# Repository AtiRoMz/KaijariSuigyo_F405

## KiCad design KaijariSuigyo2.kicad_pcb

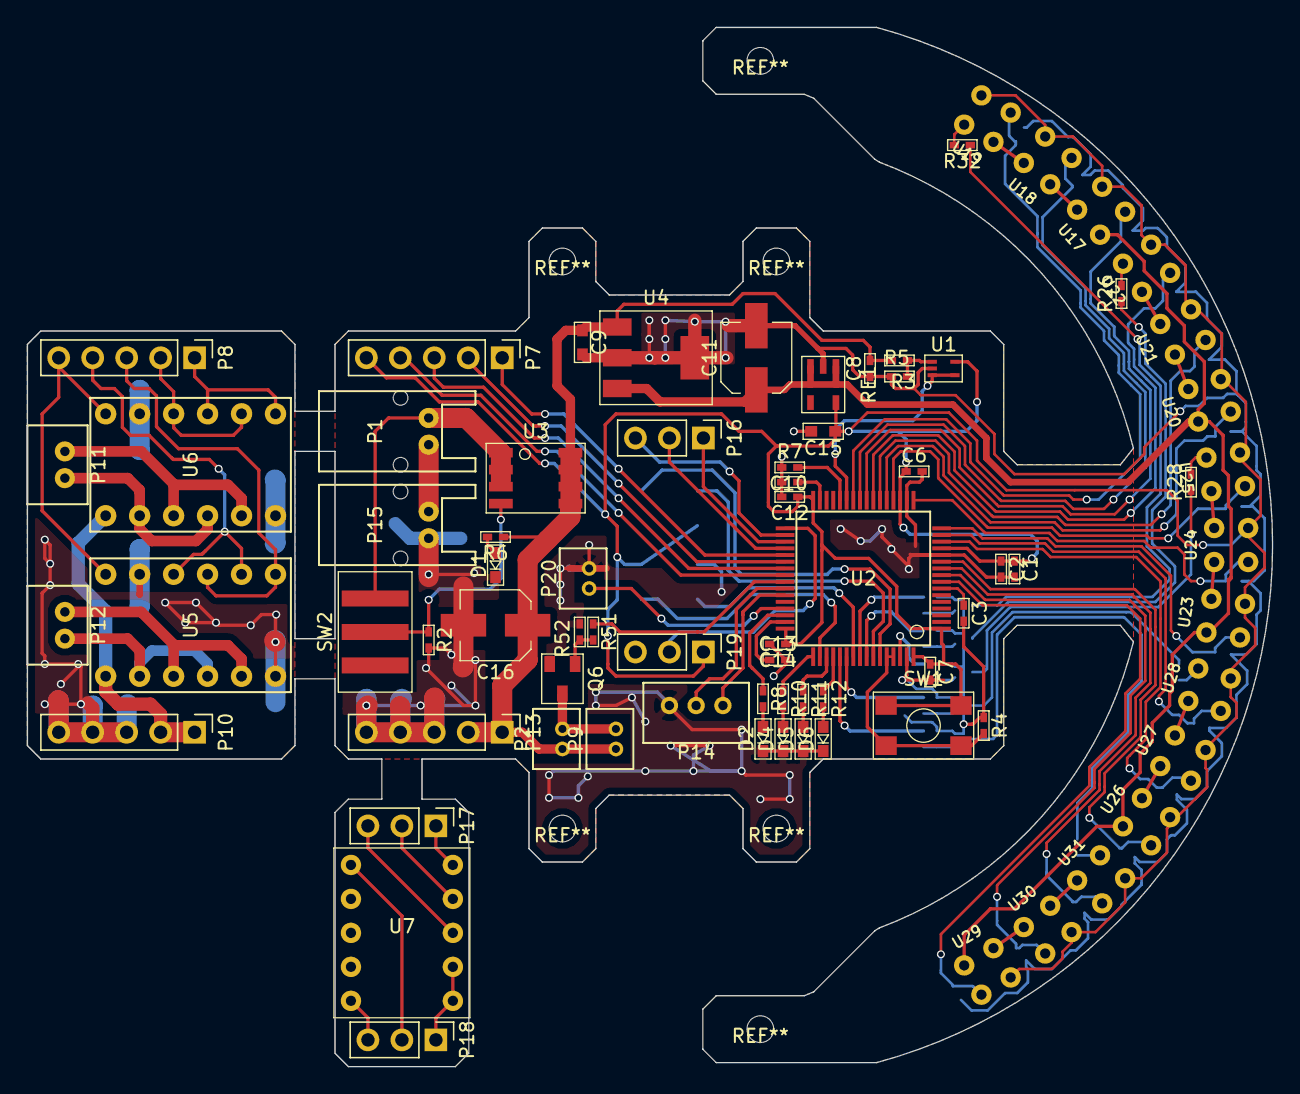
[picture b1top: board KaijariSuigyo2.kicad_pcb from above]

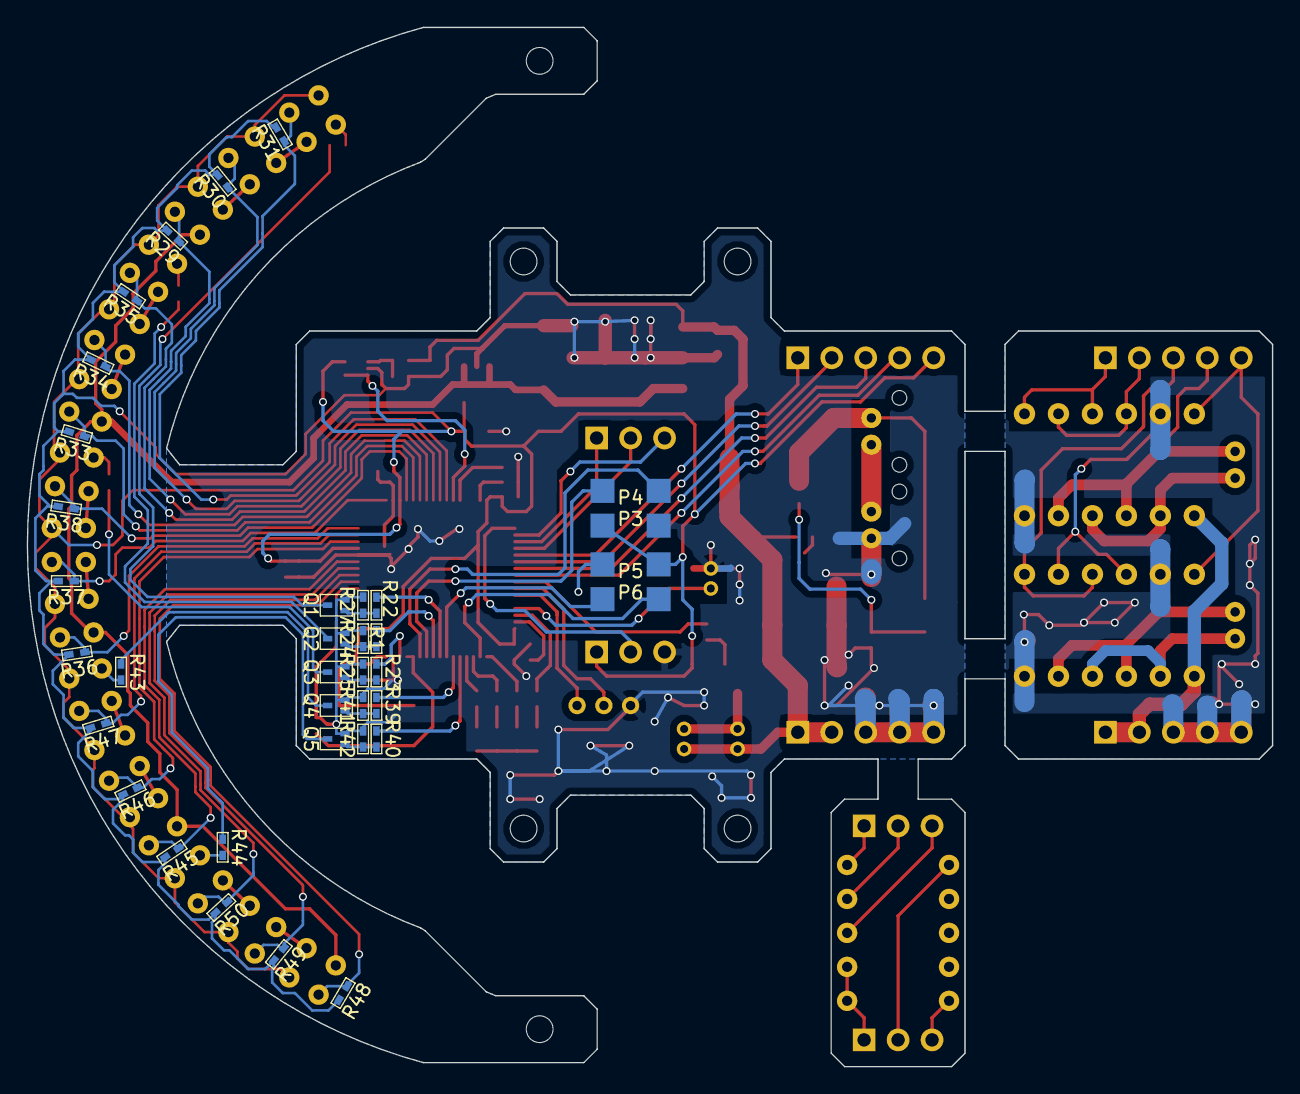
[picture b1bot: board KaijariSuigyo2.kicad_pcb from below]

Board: 2 copper layers, 93.1 x 77.7 mm, 112 parts (36 on the bottom side), 103 nets.

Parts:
C1: 1u; My_1005
C2, C3, C6, C7, C8, C12, C14: 0.1u; My_1005
C9: 0.47u; My_1608
C10, C13: 2.2u; My_1005
C11, C16: 47u; My_AlumiCapa_5mm
C15: 4.7u; My_1608
D1: Led_Small; My_LED_1608
D2, D4, D5, D6: LED; My_LED_1608
P1, P15: CONN_BATT; PA_2
P2: LEFT_FAN; ZH_2
P3, P4, P5, P6: ENC_CON; ENC_CON_ver2
P7, P8, P10, P13: CONN_01X05; Pin_Header_Straight_1x05_Pitch2.54mm
P9: RIGHT_FAN; ZH_2
P11: MOTOR_R; PH_2
P12: MOTOR_L; PH_2
P14: CONN_01X03; PH_3
P16, P17, P18, P19: CONN_01X03; Pin_Header_Straight_1x03_Pitch2.54mm
P20: CONN_01X02; ZH_2
Q1, Q2, Q3, Q4, Q5: IRLML6344; RUM003N02
Q6: IRLML6344; My_SOT-23
R1, R22, R23, R39, R40: 470; My_1005
R2: 47k; My_1005
R3: 4.7k; My_1005
R4, R5, R7, R52: 10k; My_1005
R6, R29, R30, R31, R33, R34, R35, R36, R37, R38, R45, R46, R47, R48, R49, R50: 1k; My_1005
R8, R10, R11, R12, R51: 100; My_1005
R24, R25, R27, R41, R42: 470k; My_1005
R26, R28, R32, R43, R44: 10; My_1005
RE1: MIC5219; My_SOT-23-5
SW1: SW_PUSH; TL3305
SW2: SWITCH_INV; CL-SB-22A-01
U1: BU7255HFV; My_HVSOF5
U2: STM32F405RGT6; LQFP64
U3: STS7PF30L; My_SOIC-8_3.9x4.9_Pitch1.27mm
U4: LM2940IMP; My_SOT-223
U5, U6: DRV8835_Module
U7: MPU9250_Module; MPU9250Module
U17, U18, U19, U20, U21, U22, U23, U24, U25, U26, U27, U28, U29, U30, U31: PHOTOTRANSISTOR; LBR127HLD

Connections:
+3V3: C1.1, C2.1, C6.1, C7.1, C12.1, C14.1, C15.1, P3.2, P5.2, P7.5, P19.1, RE1.5, SW1.1, U1.5, U2.1, U2.13, U2.19, U2.32, U2.48, U2.64, U17.4, U18.4, U19.4, U20.4, U21.4, U22.4, U23.4, U24.4, U25.4, U26.4, U27.4, U28.4, U29.4, U30.4, U31.4
+5V: C11.1, RE1.1, RE1.3, U4.3, U17.1, U20.1, U23.1, U26.1, U29.1
+BATT: C8.2, C9.1, C16.1, P2.1, P9.1, P13.1, P13.2, R5.2, R6.1, U3.5, U3.6, U3.7, U3.8, U4.1
BATT_REF: U1.3, U1.4, U2.27
CS: P19.2, U2.33
ENCA_LEFT: P4.1, U2.58
ENCA_RIGHT: P6.1, U2.50
ENCB_LEFT: P4.2, U2.59
ENCB_RIGHT: P6.2, U2.55
FAN_MOTOR: R51.1, U2.41
GND: C1.2, C2.2, C3.2, C6.2, C7.2, C8.1, C9.2, C10.1, C11.2, C12.2, C13.2, C14.2, C15.2, C16.2, D1.1, D2.1, D4.1, D5.1, D6.1, P3.1, P5.1, P13.3, P13.4, P13.5, P14.3, P15.1, P19.3, P20.2, Q1.2, Q2.2, Q3.2, Q4.2, Q5.2, Q6.2, R2.2, R3.1, R4.1, R7.1, R24.2, R25.2, R27.2, R29.2, R30.2, R31.2, R33.2, R34.2, R35.2, R36.2, R37.2, R38.2, R41.2, R42.2, R45.2, R46.2, R47.2, R48.2, R49.2, R50.2, R52.2, RE1.2, U1.2, U2.12, U2.18, U2.63, U4.2, U4.4
IN1_L: P7.4, U2.40
IN1_R: P7.2, U2.38
IN2_L: P7.3, U2.39
IN2_R: P7.1, U2.37
LINE_SENSOR_0: R29.1, U2.24, U17.3
LINE_SENSOR_1: R30.1, U2.25, U18.3
LINE_SENSOR_2: R31.1, U2.26, U19.3
LINE_SENSOR_3: R33.1, U2.21, U20.3
LINE_SENSOR_4: R34.1, U2.22, U21.3
LINE_SENSOR_5: R35.1, U2.23, U22.3
LINE_SENSOR_6: R36.1, U2.16, U23.3
LINE_SENSOR_7: R37.1, U2.17, U24.3
LINE_SENSOR_8: R38.1, U2.20, U25.3
LINE_SENSOR_9: R45.1, U2.11, U26.3
LINE_SENSOR_10: R46.1, U2.14, U27.3
LINE_SENSOR_11: R47.1, U2.15, U28.3
LINE_SENSOR_12: R48.1, U2.8, U29.3
LINE_SENSOR_13: R49.1, U2.9, U30.3
LINE_SENSOR_14: R50.1, U2.10, U31.3
MISO: P16.1, U2.35
MOSI: P16.2, U2.36
unnamed: C3.1, U2.7
unnamed: C10.2, U2.31
unnamed: C13.1, U2.47
unnamed: D1.2, R6.2
unnamed: D2.2, R8.2
unnamed: D4.2, R10.2
unnamed: D5.2, R11.2
unnamed: D6.2, R12.2
unnamed: P1.1, P15.2
unnamed: P1.2, SW2.1, U3.1, U3.2, U3.3
unnamed: P2.2, P9.2, Q6.3
unnamed: P8.1, U6.7, U6.9
unnamed: P8.2, U6.8, U6.10
unnamed: P8.3, U5.7, U5.9
unnamed: P8.4, U5.8, U5.10
unnamed: P8.5, U5.12, U6.12
unnamed: P10.1, P10.2, U5.1, U6.1
unnamed: P10.3, P10.4, P10.5, U5.6, U5.11, U6.6, U6.11
unnamed: P11.1, U6.2, U6.4
unnamed: P11.2, U6.3, U6.5
unnamed: P12.1, U5.2, U5.4
unnamed: P12.2, U5.3, U5.5
unnamed: P14.1, U2.43
unnamed: P14.2, U2.42
unnamed: P17.1, U7.5
unnamed: P17.2, U7.4
unnamed: P17.3, U7.3
unnamed: P18.1, U7.1, U7.2
unnamed: P18.2, U7.6
unnamed: P18.3, U7.10
unnamed: Q1.1, R22.2, R27.1
unnamed: Q1.3, R32.1
unnamed: Q2.1, R1.2, R24.1
unnamed: Q2.3, R26.1
unnamed: Q3.1, R23.2, R25.1
unnamed: Q3.3, R28.1
unnamed: Q4.1, R39.2, R41.1
unnamed: Q4.3, R43.1
unnamed: Q5.1, R40.2, R42.1
unnamed: Q5.3, R44.1
unnamed: Q6.1, R51.2, R52.1
unnamed: R2.1, SW2.2, U3.4
unnamed: R3.2, R5.1, U1.1
unnamed: R4.2, SW1.2, U2.60, U2.61
unnamed: R7.2, U2.28
unnamed: R26.2, U22.2
unnamed: R28.2, U25.2
unnamed: R32.2, U19.2
unnamed: R43.2, U28.2
unnamed: R44.2, U31.2
unnamed: U17.2, U18.1
unnamed: U18.2, U19.1
unnamed: U20.2, U21.1
unnamed: U21.2, U22.1
unnamed: U23.2, U24.1
unnamed: U24.2, U25.1
unnamed: U26.2, U27.1
unnamed: U27.2, U28.1
unnamed: U29.2, U30.1
unnamed: U30.2, U31.1
SCLK: P16.3, U2.34
SENS_LED0,1,2: R22.1, U2.56
SENS_LED3,4,5: R1.1, U2.57
SENS_LED6,7,8: R23.1, U2.62
SENS_LED9,10,11: R39.1, U2.54
SENS_LED12,13,14: R40.1, U2.53
UILED0: P20.1, U2.45
UILED1: R8.1, U2.46
UILED2: R10.1, U2.49
UILED3: R11.1, U2.51
UILED4: R12.1, U2.52
